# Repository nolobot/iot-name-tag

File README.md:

# iot-name-tag
A fusion of PCB art, RGBW lighting, and Zigbee to make the world's most high-performance name plate.

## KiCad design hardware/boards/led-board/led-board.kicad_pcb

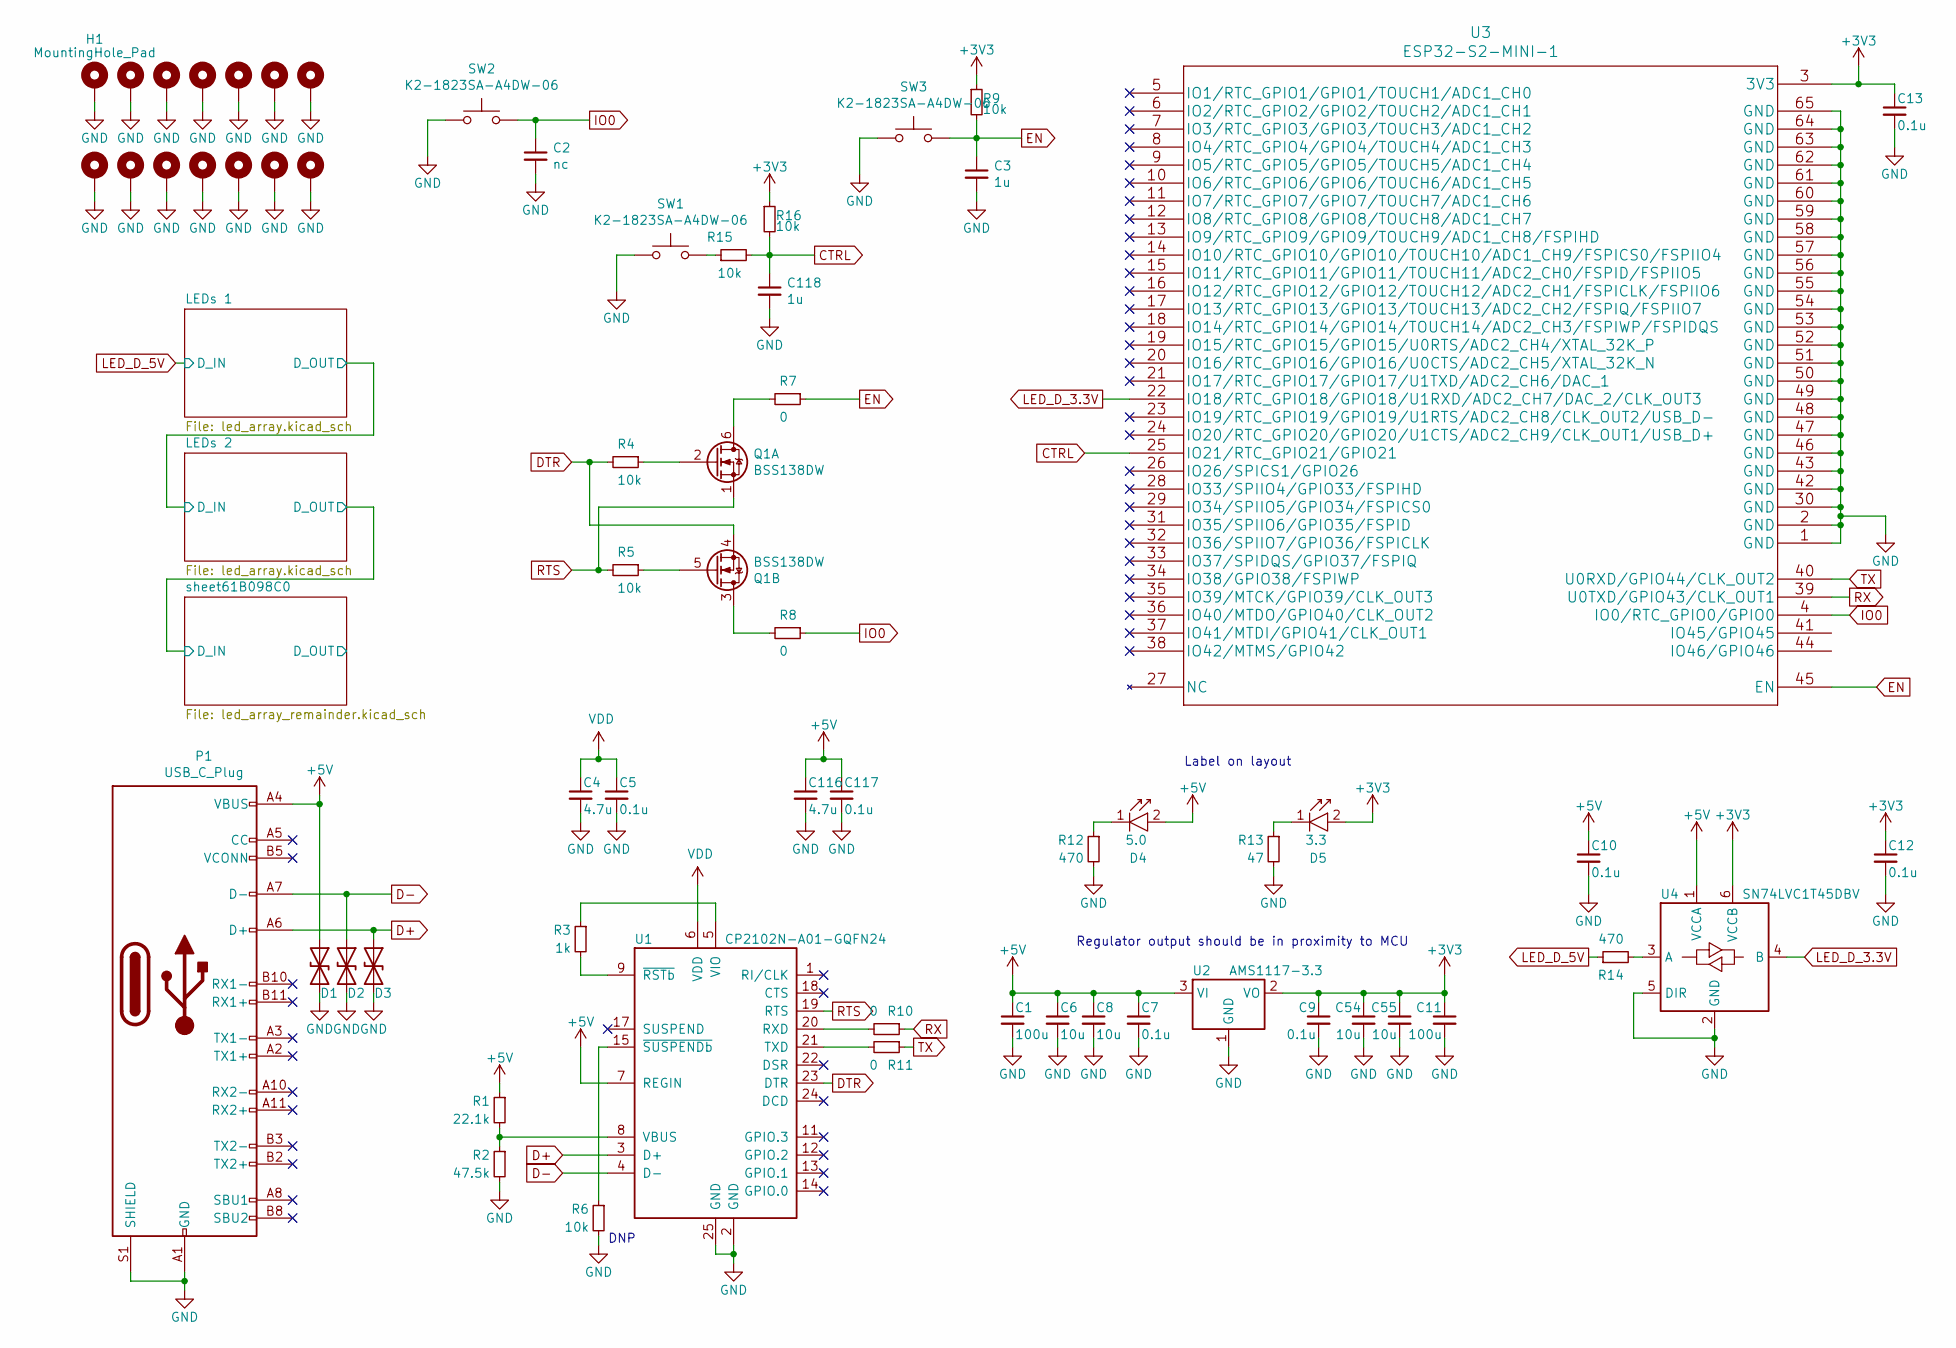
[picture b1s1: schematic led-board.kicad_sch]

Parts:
C1, C11: 100u; C_1206_3216Metric
C2: nc; C_0402_1005Metric
C3, C118: 1u; C_0402_1005Metric
C4, C116: 4.7u; C_0603_1608Metric
C5, C7, C9, C10, C12, C13, C117: 0.1u; C_0402_1005Metric
C6, C8, C54, C55: 10u; C_0603_1608Metric
D1, D2, D3: D_TVS; D_SOD-523
D4: 5.0; LED_0402_1005Metric
D5: 3.3; LED_0402_1005Metric
H1, H2, H3, H4, H5, H6, H7, H8, H9, H10, H11, H12, H13, H14: MountingHole_Pad; SMTSO-M2-2ET_Reinforced
P1: USB_C_Plug; USB_C_Receptacle_XKB_U262-16XN-4BVC11
Q1: BSS138DW; SOT-363_SC-70-6
R1: 22.1k; R_0402_1005Metric
R2: 47.5k; R_0402_1005Metric
R3: 1k; R_0402_1005Metric
R4, R5, R6, R9, R15, R16: 10k; R_0402_1005Metric
R7, R8, R10, R11: 0; R_0402_1005Metric
R12, R14: 470; R_0402_1005Metric
R13: 47; R_0402_1005Metric
SW1, SW2, SW3: K2-1823SA-A4DW-06
U1: CP2102N-A01-GQFN24; QFN-24-1EP_4x4mm_P0.5mm_EP2.6x2.6mm
U2: AMS1117-3.3; SOT-223-3_TabPin2
U3: ESP32-S2-MINI-1
U4: SN74LVC1T45DBV; SOT-23-6

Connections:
+3V3: C9.1, C11.1, C12.1, C13.1, C54.1, C55.1, D5.2 (A), R9.1, R16.1, U2.2 (VO), U3.3 (3V3), U4.6 (VCCB)
+5V: C1.1, C6.1, C7.1, C8.1, C10.1, C116.1, C117.1, D1.1 (A1), D4.2 (A), P1.A4 (VBUS), P1.A9 (VBUS), P1.B4 (VBUS), P1.B9 (VBUS), R1.1, U1.7 (REGIN), U2.3 (VI), U4.1 (VCCA); also elsewhere on the board
CTRL: C118.1, R15.2, R16.2, U3.25 (IO21/RTC_GPIO21/GPIO21)
D+: D3.1 (A1), P1.A6 (D+), U1.3 (D+)
D-: D2.1 (A1), P1.A7 (D-), U1.4 (D-)
DTR: Q1.4 (S), R4.2, U1.23 (DTR)
EN: C3.1, R7.1, R9.2, SW3.2, U3.45 (EN)
GND: C1.2, C2.2, C3.2, C4.2, C5.2, C6.2, C7.2, C8.2, C9.2, C10.2, C11.2, C12.2, C13.2, C54.2, C55.2, C116.2, C117.2, C118.2, D1.2 (A2), D2.2 (A2), D3.2 (A2), H1.1, H2.1, H3.1, H4.1, H5.1, H6.1, H7.1, H8.1, H9.1, H10.1, H11.1, H12.1, H13.1, H14.1, P1.A1 (GND), P1.A12 (GND), P1.B1 (GND), P1.B12 (GND), P1.S1 (SHIELD), R2.2, R6.2, R12.2, R13.2, SW1.1, SW2.1, SW3.1, U1.2 (GND), U1.25 (GND), U2.1 (GND), U3.1 (GND), U3.2 (GND), U3.30 (GND), U3.42 (GND), U3.43 (GND), U3.46 (GND), U3.47 (GND), U3.48 (GND), U3.49 (GND), U3.50 (GND), U3.51 (GND), U3.52 (GND), U3.53 (GND), U3.54 (GND), U3.55 (GND), U3.56 (GND), U3.57 (GND), U3.58 (GND), U3.59 (GND), U3.60 (GND), U3.61 (GND), U3.62 (GND), U3.63 (GND), U3.64 (GND), U3.65 (GND), U4.2 (GND), U4.5 (DIR); also elsewhere on the board
IO0: C2.1, R8.1, SW2.2, U3.4 (IO0/RTC_GPIO0/GPIO0)
LED_D_3.3V: U3.22 (IO18/RTC_GPIO18/GPIO18/U1RXD/ADC2_CH7/D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), U4.4 (B)
LED_D_5V: R14.1; also elsewhere on the board
unnamed: D4.1 (K), R12.1
unnamed: D5.1 (K), R13.1
unnamed: Q1.2 (G), R4.1
unnamed: Q1.3 (D), R8.2
unnamed: Q1.5 (G), R5.1
unnamed: Q1.6 (D), R7.2
unnamed: R1.2, R2.1, U1.8 (VBUS)
unnamed: R3.1, U1.5 (VIO)
unnamed: R3.2, U1.9 (~RSTb)
unnamed: R6.1, U1.15 (~SUSPENDb)
unnamed: R10.2, U1.20 (RXD)
unnamed: R11.2, U1.21 (TXD)
unnamed: R14.2, U4.3 (A)
unnamed: R15.1, SW1.2
RTS: Q1.1 (S), R5.2, U1.19 (RTS)
RX: R10.1, U3.39 (U0TXD/GPIO43/CLK_OUT1)
TX: R11.1, U3.40 (U0RXD/GPIO44/CLK_OUT2)
VDD: C4.1, C5.1, U1.6 (VDD)

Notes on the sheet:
DNP
Regulator output should be in proximity to MCU
Label on layout

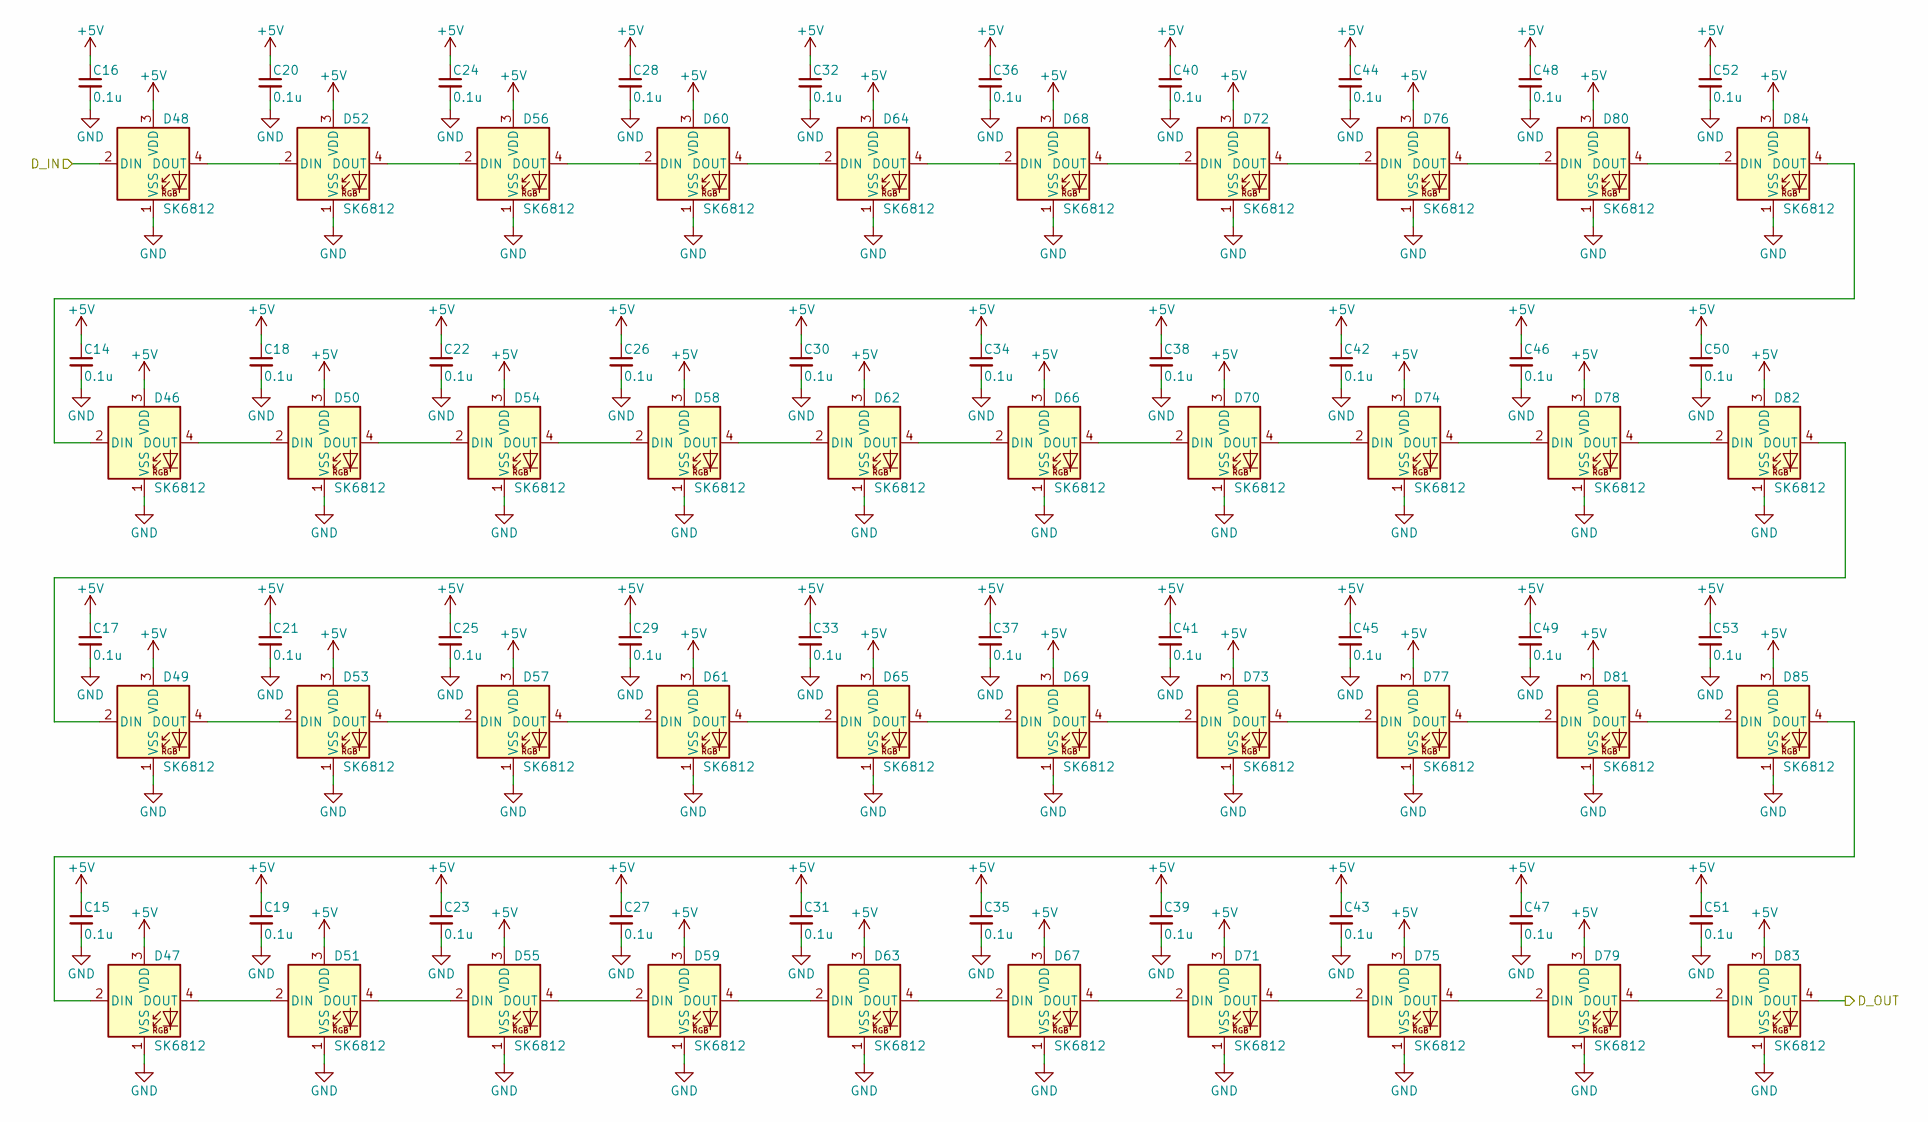
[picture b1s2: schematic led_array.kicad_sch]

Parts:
C14, C15, C16, C17, C18, C19, C20, C21, C22, C23, C24, C25, C26, C27, C28, C29, C30, C31, C32, C33, C34, C35, C36, C37, C38, C39, C40, C41, C42, C43, C44, C45, C46, C47, C48, C49, C50, C51, C52, C53: 0.1u; C_0402_NoSilk
D46, D47, D48, D49, D50, D51, D52, D53, D54, D55, D56, D57, D58, D59, D60, D61, D62, D63, D64, D65, D66, D67, D68, D69, D70, D71, D72, D73, D74, D75, D76, D77, D78, D79, D80, D81, D82, D83, D84, D85: SK6812; LED_SK6812_PLCC4_5.0x5.0mm_P3.2mm_CustomForLedArray

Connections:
+5V: C14.1, C15.1, C16.1, C17.1, C18.1, C19.1, C20.1, C21.1, C22.1, C23.1, C24.1, C25.1, C26.1, C27.1, C28.1, C29.1, C30.1, C31.1, C32.1, C33.1, C34.1, C35.1, C36.1, C37.1, C38.1, C39.1, C40.1, C41.1, C42.1, C43.1, C44.1, C45.1, C46.1, C47.1, C48.1, C49.1, C50.1, C51.1, C52.1, C53.1, D46.3 (VDD), D47.3 (VDD), D48.3 (VDD), D49.3 (VDD), D50.3 (VDD), D51.3 (VDD), D52.3 (VDD), D53.3 (VDD), D54.3 (VDD), D55.3 (VDD), D56.3 (VDD), D57.3 (VDD), D58.3 (VDD), D59.3 (VDD), D60.3 (VDD), D61.3 (VDD), D62.3 (VDD), D63.3 (VDD), D64.3 (VDD), D65.3 (VDD), D66.3 (VDD), D67.3 (VDD), D68.3 (VDD), D69.3 (VDD), D70.3 (VDD), D71.3 (VDD), D72.3 (VDD), D73.3 (VDD), D74.3 (VDD), D75.3 (VDD), D76.3 (VDD), D77.3 (VDD), D78.3 (VDD), D79.3 (VDD), D80.3 (VDD), D81.3 (VDD), D82.3 (VDD), D83.3 (VDD), D84.3 (VDD), D85.3 (VDD); also elsewhere on the board
/LEDs 2/D_IN: D48.2 (DIN); also elsewhere on the board
/sheet61B098C0/D_IN: D83.4 (DOUT); also elsewhere on the board
GND: C14.2, C15.2, C16.2, C17.2, C18.2, C19.2, C20.2, C21.2, C22.2, C23.2, C24.2, C25.2, C26.2, C27.2, C28.2, C29.2, C30.2, C31.2, C32.2, C33.2, C34.2, C35.2, C36.2, C37.2, C38.2, C39.2, C40.2, C41.2, C42.2, C43.2, C44.2, C45.2, C46.2, C47.2, C48.2, C49.2, C50.2, C51.2, C52.2, C53.2, D46.1 (VSS), D47.1 (VSS), D48.1 (VSS), D49.1 (VSS), D50.1 (VSS), D51.1 (VSS), D52.1 (VSS), D53.1 (VSS), D54.1 (VSS), D55.1 (VSS), D56.1 (VSS), D57.1 (VSS), D58.1 (VSS), D59.1 (VSS), D60.1 (VSS), D61.1 (VSS), D62.1 (VSS), D63.1 (VSS), D64.1 (VSS), D65.1 (VSS), D66.1 (VSS), D67.1 (VSS), D68.1 (VSS), D69.1 (VSS), D70.1 (VSS), D71.1 (VSS), D72.1 (VSS), D73.1 (VSS), D74.1 (VSS), D75.1 (VSS), D76.1 (VSS), D77.1 (VSS), D78.1 (VSS), D79.1 (VSS), D80.1 (VSS), D81.1 (VSS), D82.1 (VSS), D83.1 (VSS), D84.1 (VSS), D85.1 (VSS); also elsewhere on the board
unnamed: D46.2 (DIN), D84.4 (DOUT)
unnamed: D46.4 (DOUT), D50.2 (DIN)
unnamed: D47.2 (DIN), D85.4 (DOUT)
unnamed: D47.4 (DOUT), D51.2 (DIN)
unnamed: D48.4 (DOUT), D52.2 (DIN)
unnamed: D49.2 (DIN), D82.4 (DOUT)
unnamed: D49.4 (DOUT), D53.2 (DIN)
unnamed: D50.4 (DOUT), D54.2 (DIN)
unnamed: D51.4 (DOUT), D55.2 (DIN)
unnamed: D52.4 (DOUT), D56.2 (DIN)
unnamed: D53.4 (DOUT), D57.2 (DIN)
unnamed: D54.4 (DOUT), D58.2 (DIN)
unnamed: D55.4 (DOUT), D59.2 (DIN)
unnamed: D56.4 (DOUT), D60.2 (DIN)
unnamed: D57.4 (DOUT), D61.2 (DIN)
unnamed: D58.4 (DOUT), D62.2 (DIN)
unnamed: D59.4 (DOUT), D63.2 (DIN)
unnamed: D60.4 (DOUT), D64.2 (DIN)
unnamed: D61.4 (DOUT), D65.2 (DIN)
unnamed: D62.4 (DOUT), D66.2 (DIN)
unnamed: D63.4 (DOUT), D67.2 (DIN)
unnamed: D64.4 (DOUT), D68.2 (DIN)
unnamed: D65.4 (DOUT), D69.2 (DIN)
unnamed: D66.4 (DOUT), D70.2 (DIN)
unnamed: D67.4 (DOUT), D71.2 (DIN)
unnamed: D68.4 (DOUT), D72.2 (DIN)
unnamed: D69.4 (DOUT), D73.2 (DIN)
unnamed: D70.4 (DOUT), D74.2 (DIN)
unnamed: D71.4 (DOUT), D75.2 (DIN)
unnamed: D72.4 (DOUT), D76.2 (DIN)
unnamed: D73.4 (DOUT), D77.2 (DIN)
unnamed: D74.4 (DOUT), D78.2 (DIN)
unnamed: D75.4 (DOUT), D79.2 (DIN)
unnamed: D76.4 (DOUT), D80.2 (DIN)
unnamed: D77.4 (DOUT), D81.2 (DIN)
unnamed: D78.4 (DOUT), D82.2 (DIN)
unnamed: D79.4 (DOUT), D83.2 (DIN)
unnamed: D80.4 (DOUT), D84.2 (DIN)
unnamed: D81.4 (DOUT), D85.2 (DIN)

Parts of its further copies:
C56, C57, C58, C59, C60, C61, C62, C63, C64, C65, C66, C67, C68, C69, C70, C71, C72, C73, C74, C75, C76, C77, C78, C79, C80, C81, C82, C83, C84, C85, C86, C87, C88, C89, C90, C91, C92, C93, C94, C95: 0.1u; C_0402_NoSilk
D6, D7, D8, D9, D10, D11, D12, D13, D14, D15, D16, D17, D18, D19, D20, D21, D22, D23, D24, D25, D26, D27, D28, D29, D30, D31, D32, D33, D34, D35, D36, D37, D38, D39, D40, D41, D42, D43, D44, D45: SK6812; LED_SK6812_PLCC4_5.0x5.0mm_P3.2mm_CustomForLedArray

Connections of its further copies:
+5V: C56.1, C57.1, C58.1, C59.1, C60.1, C61.1, C62.1, C63.1, C64.1, C65.1, C66.1, C67.1, C68.1, C69.1, C70.1, C71.1, C72.1, C73.1, C74.1, C75.1, C76.1, C77.1, C78.1, C79.1, C80.1, C81.1, C82.1, C83.1, C84.1, C85.1, C86.1, C87.1, C88.1, C89.1, C90.1, C91.1, C92.1, C93.1, C94.1, C95.1, D6.3 (VDD), D7.3 (VDD), D8.3 (VDD), D9.3 (VDD), D10.3 (VDD), D11.3 (VDD), D12.3 (VDD), D13.3 (VDD), D14.3 (VDD), D15.3 (VDD), D16.3 (VDD), D17.3 (VDD), D18.3 (VDD), D19.3 (VDD), D20.3 (VDD), D21.3 (VDD), D22.3 (VDD), D23.3 (VDD), D24.3 (VDD), D25.3 (VDD), D26.3 (VDD), D27.3 (VDD), D28.3 (VDD), D29.3 (VDD), D30.3 (VDD), D31.3 (VDD), D32.3 (VDD), D33.3 (VDD), D34.3 (VDD), D35.3 (VDD), D36.3 (VDD), D37.3 (VDD), D38.3 (VDD), D39.3 (VDD), D40.3 (VDD), D41.3 (VDD), D42.3 (VDD), D43.3 (VDD), D44.3 (VDD), D45.3 (VDD); also elsewhere on the board
/LEDs 2/D_IN: D43.4 (DOUT); also elsewhere on the board
GND: C56.2, C57.2, C58.2, C59.2, C60.2, C61.2, C62.2, C63.2, C64.2, C65.2, C66.2, C67.2, C68.2, C69.2, C70.2, C71.2, C72.2, C73.2, C74.2, C75.2, C76.2, C77.2, C78.2, C79.2, C80.2, C81.2, C82.2, C83.2, C84.2, C85.2, C86.2, C87.2, C88.2, C89.2, C90.2, C91.2, C92.2, C93.2, C94.2, C95.2, D6.1 (VSS), D7.1 (VSS), D8.1 (VSS), D9.1 (VSS), D10.1 (VSS), D11.1 (VSS), D12.1 (VSS), D13.1 (VSS), D14.1 (VSS), D15.1 (VSS), D16.1 (VSS), D17.1 (VSS), D18.1 (VSS), D19.1 (VSS), D20.1 (VSS), D21.1 (VSS), D22.1 (VSS), D23.1 (VSS), D24.1 (VSS), D25.1 (VSS), D26.1 (VSS), D27.1 (VSS), D28.1 (VSS), D29.1 (VSS), D30.1 (VSS), D31.1 (VSS), D32.1 (VSS), D33.1 (VSS), D34.1 (VSS), D35.1 (VSS), D36.1 (VSS), D37.1 (VSS), D38.1 (VSS), D39.1 (VSS), D40.1 (VSS), D41.1 (VSS), D42.1 (VSS), D43.1 (VSS), D44.1 (VSS), D45.1 (VSS); also elsewhere on the board
LED_D_5V: D8.2 (DIN); also elsewhere on the board
unnamed: D6.4 (DOUT), D10.2 (DIN)
unnamed: D10.4 (DOUT), D14.2 (DIN)
unnamed: D7.4 (DOUT), D11.2 (DIN)
unnamed: D11.4 (DOUT), D15.2 (DIN)
unnamed: D8.4 (DOUT), D12.2 (DIN)
unnamed: D12.4 (DOUT), D16.2 (DIN)
unnamed: D9.4 (DOUT), D13.2 (DIN)
unnamed: D13.4 (DOUT), D17.2 (DIN)
unnamed: D14.4 (DOUT), D18.2 (DIN)
unnamed: D15.4 (DOUT), D19.2 (DIN)
unnamed: D16.4 (DOUT), D20.2 (DIN)
unnamed: D17.4 (DOUT), D21.2 (DIN)
unnamed: D18.4 (DOUT), D22.2 (DIN)
unnamed: D19.4 (DOUT), D23.2 (DIN)
unnamed: D20.4 (DOUT), D24.2 (DIN)
unnamed: D21.4 (DOUT), D25.2 (DIN)
unnamed: D22.4 (DOUT), D26.2 (DIN)
unnamed: D23.4 (DOUT), D27.2 (DIN)
unnamed: D24.4 (DOUT), D28.2 (DIN)
unnamed: D25.4 (DOUT), D29.2 (DIN)
unnamed: D26.4 (DOUT), D30.2 (DIN)
unnamed: D27.4 (DOUT), D31.2 (DIN)
unnamed: D28.4 (DOUT), D32.2 (DIN)
unnamed: D29.4 (DOUT), D33.2 (DIN)
unnamed: D30.4 (DOUT), D34.2 (DIN)
unnamed: D31.4 (DOUT), D35.2 (DIN)
unnamed: D32.4 (DOUT), D36.2 (DIN)
unnamed: D33.4 (DOUT), D37.2 (DIN)
unnamed: D34.4 (DOUT), D38.2 (DIN)
unnamed: D35.4 (DOUT), D39.2 (DIN)
unnamed: D36.4 (DOUT), D40.2 (DIN)
unnamed: D37.4 (DOUT), D41.2 (DIN)
unnamed: D38.4 (DOUT), D42.2 (DIN)
unnamed: D39.4 (DOUT), D43.2 (DIN)
unnamed: D40.4 (DOUT), D44.2 (DIN)
unnamed: D41.4 (DOUT), D45.2 (DIN)
unnamed: D9.2 (DIN), D42.4 (DOUT)
unnamed: D6.2 (DIN), D44.4 (DOUT)
unnamed: D7.2 (DIN), D45.4 (DOUT)

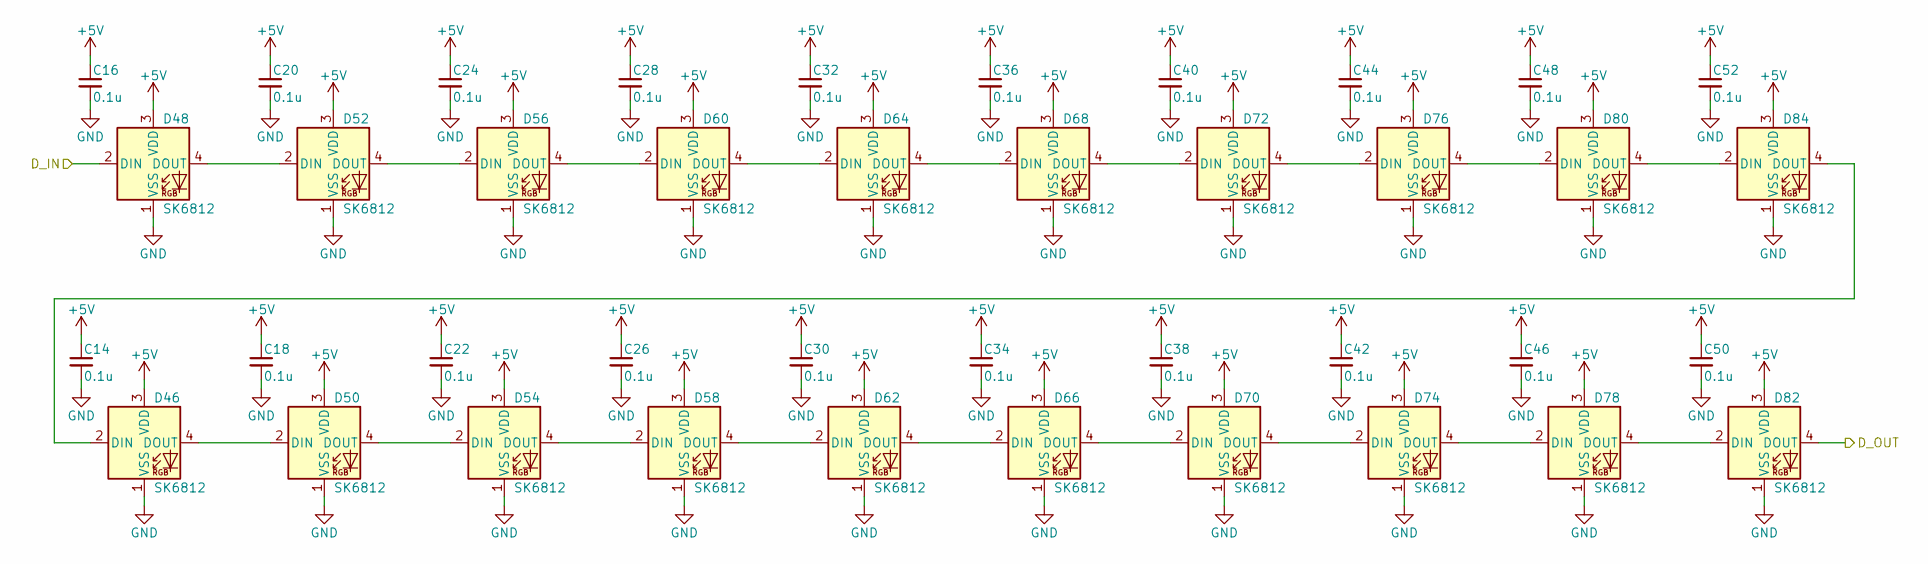
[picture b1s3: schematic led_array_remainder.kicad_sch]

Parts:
C14, C16, C18, C20, C22, C24, C26, C28, C30, C32, C34, C36, C38, C40, C42, C44, C46, C48, C50, C52: 0.1u; C_0402_NoSilk
D46, D48, D50, D52, D54, D56, D58, D60, D62, D64, D66, D68, D70, D72, D74, D76, D78, D80, D82, D84: SK6812; LED_SK6812_PLCC4_5.0x5.0mm_P3.2mm_CustomForLedArray

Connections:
+5V: C14.1, C16.1, C18.1, C20.1, C22.1, C24.1, C26.1, C28.1, C30.1, C32.1, C34.1, C36.1, C38.1, C40.1, C42.1, C44.1, C46.1, C48.1, C50.1, C52.1, D46.3 (VDD), D48.3 (VDD), D50.3 (VDD), D52.3 (VDD), D54.3 (VDD), D56.3 (VDD), D58.3 (VDD), D60.3 (VDD), D62.3 (VDD), D64.3 (VDD), D66.3 (VDD), D68.3 (VDD), D70.3 (VDD), D72.3 (VDD), D74.3 (VDD), D76.3 (VDD), D78.3 (VDD), D80.3 (VDD), D82.3 (VDD), D84.3 (VDD); also elsewhere on the board
/LEDs 2/D_IN: D48.2 (DIN); also elsewhere on the board
GND: C14.2, C16.2, C18.2, C20.2, C22.2, C24.2, C26.2, C28.2, C30.2, C32.2, C34.2, C36.2, C38.2, C40.2, C42.2, C44.2, C46.2, C48.2, C50.2, C52.2, D46.1 (VSS), D48.1 (VSS), D50.1 (VSS), D52.1 (VSS), D54.1 (VSS), D56.1 (VSS), D58.1 (VSS), D60.1 (VSS), D62.1 (VSS), D64.1 (VSS), D66.1 (VSS), D68.1 (VSS), D70.1 (VSS), D72.1 (VSS), D74.1 (VSS), D76.1 (VSS), D78.1 (VSS), D80.1 (VSS), D82.1 (VSS), D84.1 (VSS); also elsewhere on the board
unnamed: D46.2 (DIN), D84.4 (DOUT)
unnamed: D46.4 (DOUT), D50.2 (DIN)
unnamed: D48.4 (DOUT), D52.2 (DIN)
unnamed 60: D82.4 (DOUT); also elsewhere on the board
unnamed: D50.4 (DOUT), D54.2 (DIN)
unnamed: D52.4 (DOUT), D56.2 (DIN)
unnamed: D54.4 (DOUT), D58.2 (DIN)
unnamed: D56.4 (DOUT), D60.2 (DIN)
unnamed: D58.4 (DOUT), D62.2 (DIN)
unnamed: D60.4 (DOUT), D64.2 (DIN)
unnamed: D62.4 (DOUT), D66.2 (DIN)
unnamed: D64.4 (DOUT), D68.2 (DIN)
unnamed: D66.4 (DOUT), D70.2 (DIN)
unnamed: D68.4 (DOUT), D72.2 (DIN)
unnamed: D70.4 (DOUT), D74.2 (DIN)
unnamed: D72.4 (DOUT), D76.2 (DIN)
unnamed: D74.4 (DOUT), D78.2 (DIN)
unnamed: D76.4 (DOUT), D80.2 (DIN)
unnamed: D78.4 (DOUT), D82.2 (DIN)
unnamed: D80.4 (DOUT), D84.2 (DIN)

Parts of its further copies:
C56, C58, C60, C62, C64, C66, C68, C70, C72, C74, C76, C78, C80, C82, C84, C86, C88, C90, C92, C94, C96, C97, C98, C99, C100, C101, C102, C103, C104, C105, C106, C107, C108, C109, C110, C111, C112, C113, C114, C115: 0.1u; C_0402_NoSilk
D6, D8, D10, D12, D14, D16, D18, D20, D22, D24, D26, D28, D30, D32, D34, D36, D38, D40, D42, D44, D86, D87, D88, D89, D90, D91, D92, D93, D94, D95, D96, D97, D98, D99, D100, D101, D102, D103, D104, D105: SK6812; LED_SK6812_PLCC4_5.0x5.0mm_P3.2mm_CustomForLedArray

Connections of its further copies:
+5V: C56.1, C58.1, C60.1, C62.1, C64.1, C66.1, C68.1, C70.1, C72.1, C74.1, C76.1, C78.1, C80.1, C82.1, C84.1, C86.1, C88.1, C90.1, C92.1, C94.1, C96.1, C97.1, C98.1, C99.1, C100.1, C101.1, C102.1, C103.1, C104.1, C105.1, C106.1, C107.1, C108.1, C109.1, C110.1, C111.1, C112.1, C113.1, C114.1, C115.1, D6.3 (VDD), D8.3 (VDD), D10.3 (VDD), D12.3 (VDD), D14.3 (VDD), D16.3 (VDD), D18.3 (VDD), D20.3 (VDD), D22.3 (VDD), D24.3 (VDD), D26.3 (VDD), D28.3 (VDD), D30.3 (VDD), D32.3 (VDD), D34.3 (VDD), D36.3 (VDD), D38.3 (VDD), D40.3 (VDD), D42.3 (VDD), D44.3 (VDD), D86.3 (VDD), D87.3 (VDD), D88.3 (VDD), D89.3 (VDD), D90.3 (VDD), D91.3 (VDD), D92.3 (VDD), D93.3 (VDD), D94.3 (VDD), D95.3 (VDD), D96.3 (VDD), D97.3 (VDD), D98.3 (VDD), D99.3 (VDD), D100.3 (VDD), D101.3 (VDD), D102.3 (VDD), D103.3 (VDD), D104.3 (VDD), D105.3 (VDD); also elsewhere on the board
/sheet61B098C0/D_IN: D87.2 (DIN); also elsewhere on the board
/sheet61B098C0/D_OUT: D104.4 (DOUT)
GND: C56.2, C58.2, C60.2, C62.2, C64.2, C66.2, C68.2, C70.2, C72.2, C74.2, C76.2, C78.2, C80.2, C82.2, C84.2, C86.2, C88.2, C90.2, C92.2, C94.2, C96.2, C97.2, C98.2, C99.2, C100.2, C101.2, C102.2, C103.2, C104.2, C105.2, C106.2, C107.2, C108.2, C109.2, C110.2, C111.2, C112.2, C113.2, C114.2, C115.2, D6.1 (VSS), D8.1 (VSS), D10.1 (VSS), D12.1 (VSS), D14.1 (VSS), D16.1 (VSS), D18.1 (VSS), D20.1 (VSS), D22.1 (VSS), D24.1 (VSS), D26.1 (VSS), D28.1 (VSS), D30.1 (VSS), D32.1 (VSS), D34.1 (VSS), D36.1 (VSS), D38.1 (VSS), D40.1 (VSS), D42.1 (VSS), D44.1 (VSS), D86.1 (VSS), D87.1 (VSS), D88.1 (VSS), D89.1 (VSS), D90.1 (VSS), D91.1 (VSS), D92.1 (VSS), D93.1 (VSS), D94.1 (VSS), D95.1 (VSS), D96.1 (VSS), D97.1 (VSS), D98.1 (VSS), D99.1 (VSS), D100.1 (VSS), D101.1 (VSS), D102.1 (VSS), D103.1 (VSS), D104.1 (VSS), D105.1 (VSS); also elsewhere on the board
LED_D_5V: D8.2 (DIN); also elsewhere on the board
unnamed: D6.4 (DOUT), D10.2 (DIN)
unnamed: D10.4 (DOUT), D14.2 (DIN)
unnamed: D8.4 (DOUT), D12.2 (DIN)
unnamed: D12.4 (DOUT), D16.2 (DIN)
unnamed: D14.4 (DOUT), D18.2 (DIN)
unnamed: D16.4 (DOUT), D20.2 (DIN)
unnamed: D18.4 (DOUT), D22.2 (DIN)
unnamed: D20.4 (DOUT), D24.2 (DIN)
unnamed: D22.4 (DOUT), D26.2 (DIN)
unnamed: D24.4 (DOUT), D28.2 (DIN)
unnamed: D26.4 (DOUT), D30.2 (DIN)
unnamed: D28.4 (DOUT), D32.2 (DIN)
unnamed: D30.4 (DOUT), D34.2 (DIN)
unnamed: D32.4 (DOUT), D36.2 (DIN)
unnamed: D34.4 (DOUT), D38.2 (DIN)
unnamed: D36.4 (DOUT), D40.2 (DIN)
unnamed: D38.4 (DOUT), D42.2 (DIN)
unnamed: D40.4 (DOUT), D44.2 (DIN)
unnamed 52: D42.4 (DOUT); also elsewhere on the board
unnamed: D6.2 (DIN), D44.4 (DOUT)
unnamed: D86.4 (DOUT), D88.2 (DIN)
unnamed: D87.4 (DOUT), D89.2 (DIN)
unnamed: D88.4 (DOUT), D90.2 (DIN)
unnamed: D89.4 (DOUT), D91.2 (DIN)
unnamed: D90.4 (DOUT), D92.2 (DIN)
unnamed: D91.4 (DOUT), D93.2 (DIN)
unnamed: D92.4 (DOUT), D94.2 (DIN)
unnamed: D93.4 (DOUT), D95.2 (DIN)
unnamed: D94.4 (DOUT), D96.2 (DIN)
unnamed: D95.4 (DOUT), D97.2 (DIN)
unnamed: D96.4 (DOUT), D98.2 (DIN)
unnamed: D97.4 (DOUT), D99.2 (DIN)
unnamed: D98.4 (DOUT), D100.2 (DIN)
unnamed: D100.4 (DOUT), D102.2 (DIN)
unnamed: D99.4 (DOUT), D101.2 (DIN)
unnamed: D101.4 (DOUT), D103.2 (DIN)
unnamed: D102.4 (DOUT), D104.2 (DIN)
unnamed: D103.4 (DOUT), D105.2 (DIN)
unnamed: D86.2 (DIN), D105.4 (DOUT)

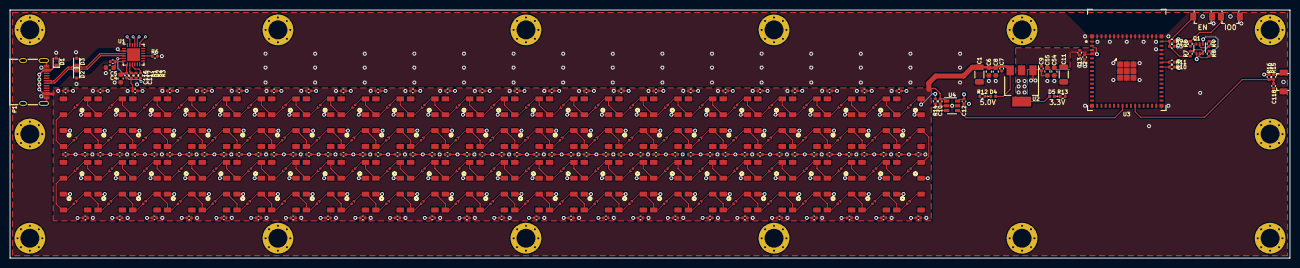
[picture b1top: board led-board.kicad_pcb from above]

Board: 4 copper layers, 258.0 x 50.0 mm, 262 parts (0 on the bottom side), 128 nets.

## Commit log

2024-11-21 Add hardware from Rev A
2024-11-22 Add ESP-IDF v5.3.1
2024-11-22 Add and clean up basic home assistant zigbee example showcasing Espressif Zigbee usage with Home Assistant
2024-11-23 Test push from personal laptop
2024-11-25 Add hardware architecture diagrams
2024-11-25 Add gitignore for skipping lck files from Kicad
